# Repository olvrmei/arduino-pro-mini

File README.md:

<h1 align="center">KiCad Arduino Pro Mini</h1>

<br />

KiCad project for an university assignment of something more or less close to an Arduino Pro Mini board clone.
The assignment required to build at least one custom library for a component. The component chosen was the MIC5205.
Again this is not an exact clone but a fun first project to learn how to use the software for schematic capture and PCB Layout.

Schematic reference: https://www.arduino.cc/en/uploads/Main/Arduino-Pro-Mini-schematic.pdf

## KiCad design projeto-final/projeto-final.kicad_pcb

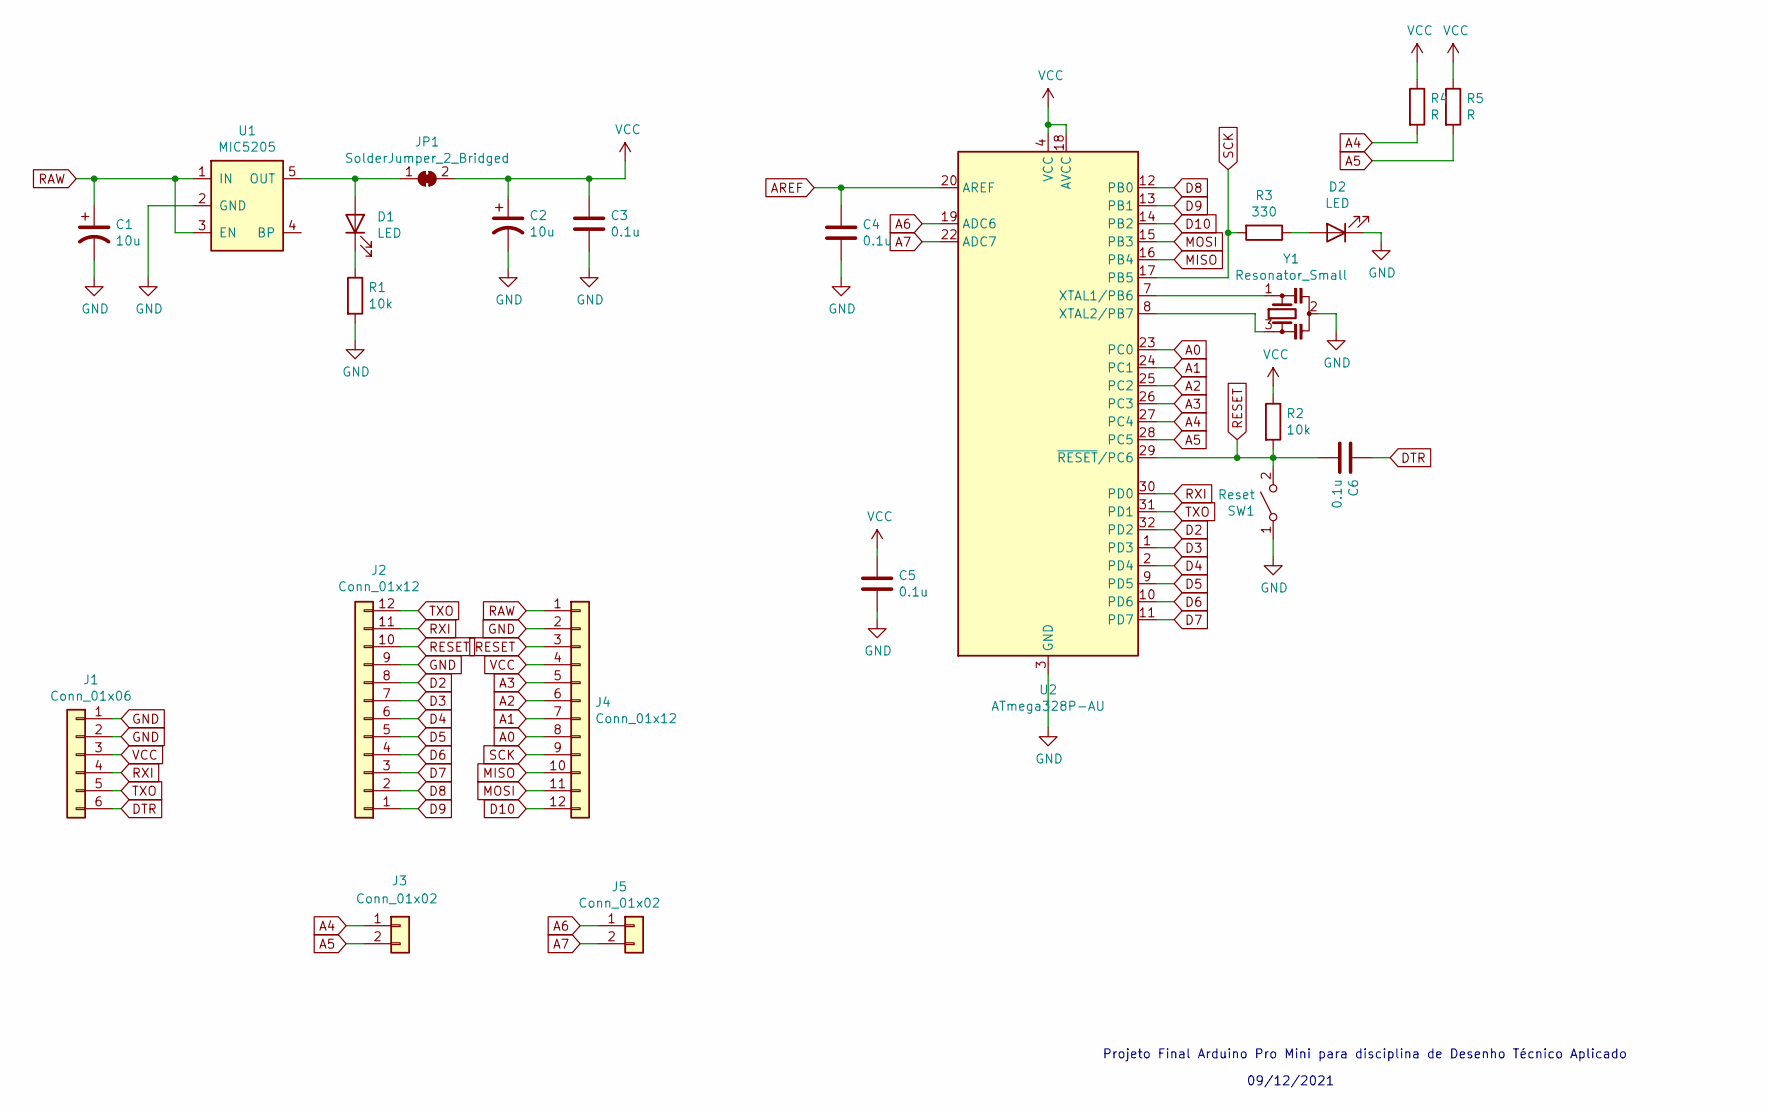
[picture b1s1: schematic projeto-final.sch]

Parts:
C1, C2: 10u; C_1206_3216Metric
C3, C4, C5, C6: 0.1u; C_0603_1608Metric
D1, D2: LED; LED_0603_1608Metric
J1: Conn_01x06; Conn_6
J2, J4: Conn_01x12; Conn_12
J3, J5: Conn_01x02; Conn_2
JP1: SolderJumper_2_Bridged; SolderJumper-2_P1.3mm_Bridged_Pad1.0x1.5mm
R1, R2: 10k; R_0603_1608Metric
R3: 330; R_0603_1608Metric
R4, R5: R; R_0603_1608Metric
SW1: Reset; SW_SPST_CK_RS282G05A3
U1: MIC5205; SOT-23-5
U2: ATmega328P-AU; TQFP-32_7x7mm_P0.8mm
Y1: Resonator_Small; Resonator_SMD_muRata_CSTxExxV-3Pin_3.0x1.1mm

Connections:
A0: J4.8, U2.23 (PC0)
A1: J4.7, U2.24 (PC1)
A2: J4.6, U2.25 (PC2)
A3: J4.5, U2.26 (PC3)
A4: J3.1, R4.2, U2.27 (PC4)
A5: J3.2, R5.2, U2.28 (PC5)
A6: J5.1, U2.19 (ADC6)
A7: J5.2, U2.22 (ADC7)
AREF: C4.1, U2.20 (AREF)
D2: J2.8, U2.32 (PD2)
D3: J2.7, U2.1 (PD3)
D4: J2.6, U2.2 (PD4)
D5: J2.5, U2.9 (PD5)
D6: J2.4, U2.10 (PD6)
D7: J2.3, U2.11 (PD7)
D8: J2.2, U2.12 (PB0)
D9: J2.1, U2.13 (PB1)
D10: J4.12, U2.14 (PB2)
DTR: C6.1, J1.6
GND: C1.2, C2.2, C3.2, C4.2, C5.2, D2.1 (K), J1.1, J1.2, J2.9, J4.2, R1.2, SW1.1 (A), U1.2 (GND), U2.3 (GND), U2.5 (GND), U2.21 (GND), Y1.2
MISO: J4.10, U2.16 (PB4)
MOSI: J4.11, U2.15 (PB3)
unnamed: D1.1 (K), R1.1
unnamed: D1.2 (A), JP1.1 (A), U1.5 (OUT)
unnamed: D2.2 (A), R3.1
unnamed: U2.7 (XTAL1/PB6), Y1.1
unnamed: U2.8 (XTAL2/PB7), Y1.3
RAW: C1.1, J4.1, U1.1 (IN), U1.3 (EN)
RESET: C6.2, J2.10, J4.3, R2.2, SW1.2 (B), U2.29 (~RESET~/PC6)
RXI: J1.4, J2.11, U2.30 (PD0)
SCK: J4.9, R3.2, U2.17 (PB5)
TXO: J1.5, J2.12, U2.31 (PD1)
VCC: C2.1, C3.1, C5.1, J1.3, J4.4, JP1.2 (B), R2.1, R4.1, R5.1, U2.4 (VCC), U2.6 (VCC), U2.18 (AVCC)

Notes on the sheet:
Projeto Final Arduino Pro Mini para disciplina de Desenho Técnico Aplicado
09/12/2021

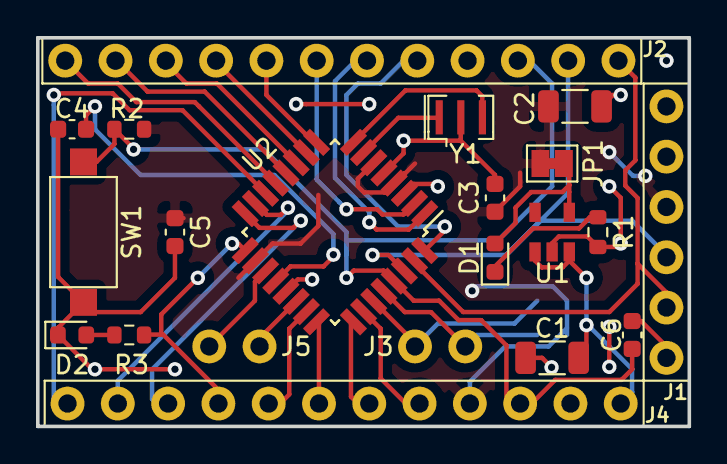
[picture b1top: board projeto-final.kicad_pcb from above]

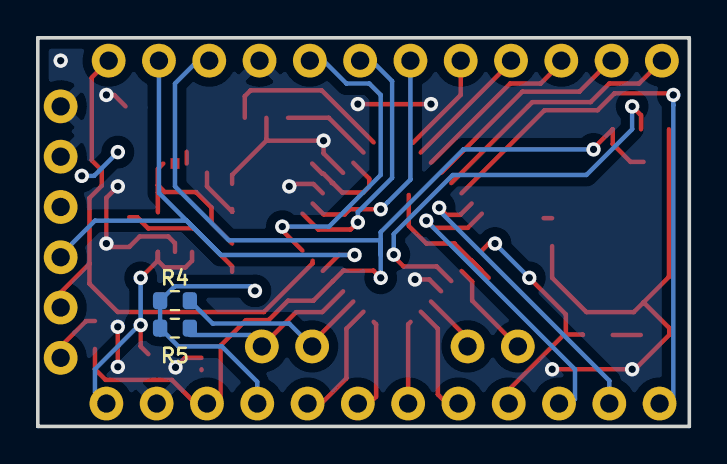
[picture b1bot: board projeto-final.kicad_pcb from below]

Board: 2 copper layers, 36.2 x 21.6 mm, 23 parts (2 on the bottom side), 33 nets.

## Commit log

2021-12-17 Project files commit
2021-12-17 Add demo gif
2021-12-17 Add board gif
